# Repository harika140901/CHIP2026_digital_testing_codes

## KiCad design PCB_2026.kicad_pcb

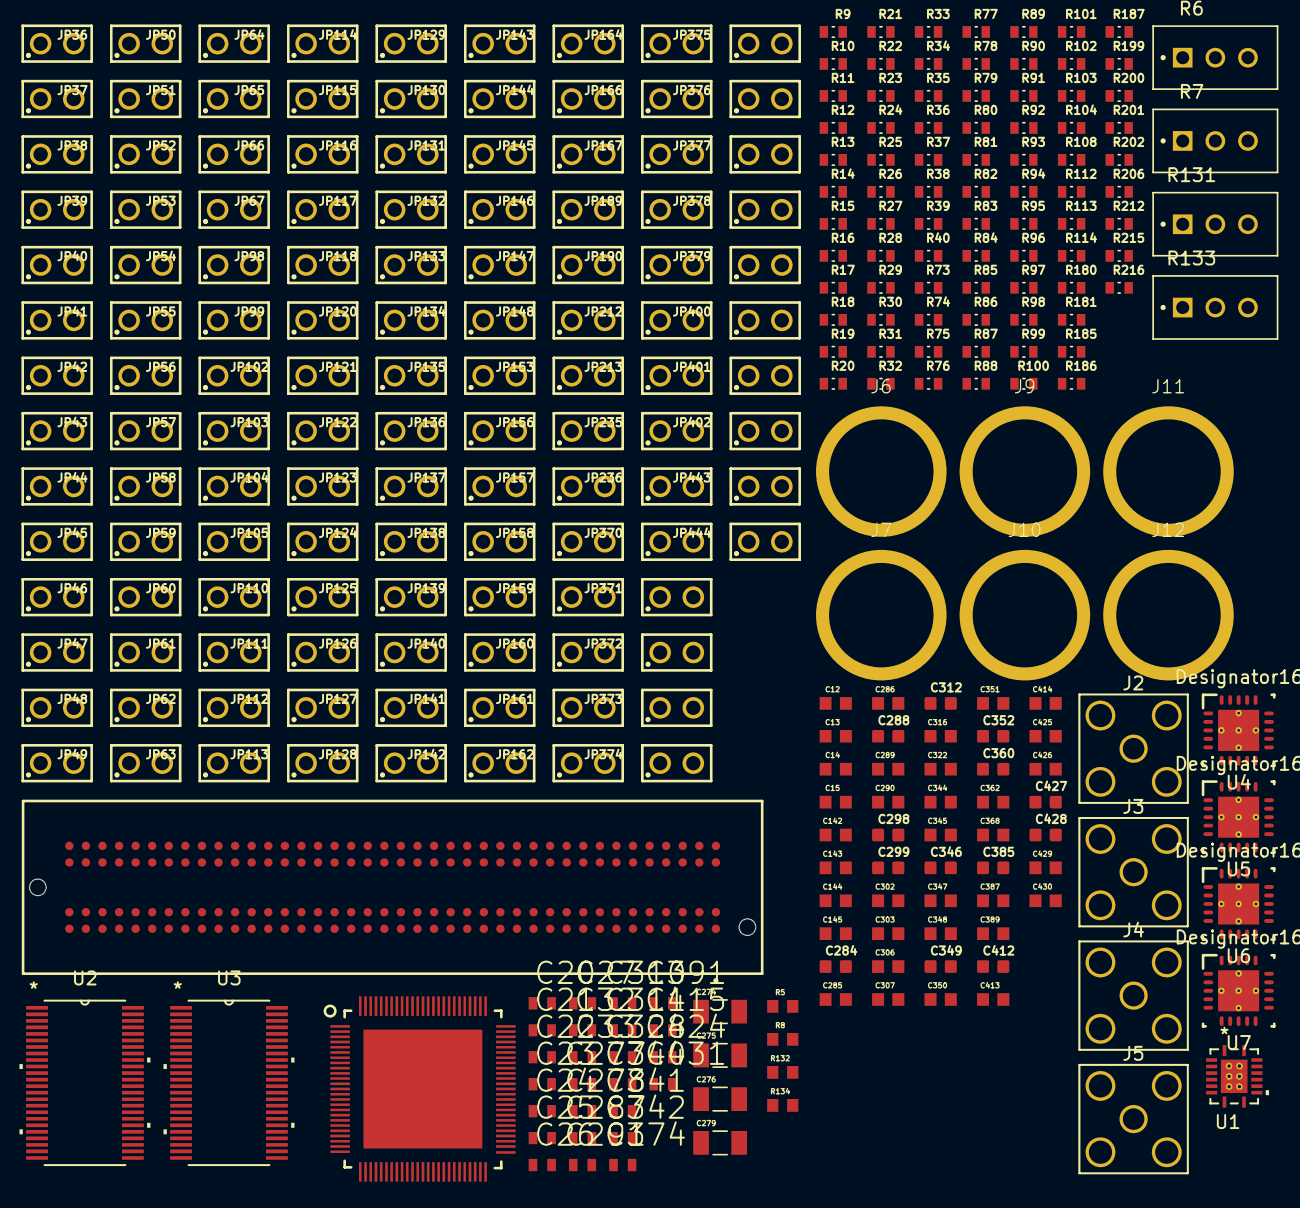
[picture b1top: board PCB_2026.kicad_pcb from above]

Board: 2 copper layers, 306 parts (0 on the bottom side), 260 nets, no tracks yet.

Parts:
C12, C14, C142, C144: 4.7u; CAPC1608X90N
C13, C15, C143, C145, C286, C290, C306, C307, C322, C345, C348, C351, C368, C389, C414, C425, C430: 1n; CAPC1608X90N
C20, C21, C22, C23, C24, C25, C26, C27, C32, C33: 1uF; CAPC1608X90N
C274, C275, C276, C279: C100u; CAPC3216X180N
C277, C278, C287, C291, C310, C311, C328, C340, C341, C342, C374, C391, C415, C424, C431: 1u; CAPC1608X90N
C284, C288, C298, C299, C312, C346, C349, C352, C360, C385, C412, C427, C428: 10n; CAPC1608X90N
C285, C289, C302, C303, C316, C344, C347, C350, C362, C387, C413, C426, C429: 100n; CAPC1608X90N
J1: ASP-134603-01; CONN160_4603-01_SAI
J2, J3, J4, J5: 142-0701-201; CONN_142-0701-201_CIN
J6, J7, J9, J10, J11, J12: BJACK
JP6, JP7, JP22, JP23, JP24, JP25, JP26, JP29, JP30, JP31, JP32, JP33, JP34, JP35, JP36, JP37, JP38, JP39, JP40, JP41, JP42, JP43, JP44, JP45, JP46, JP47, JP48, JP49, JP50, JP51, JP52, JP53, JP54, JP55, JP56, JP57, JP58, JP59, JP60, JP61, JP62, JP63, JP64, JP65, JP66, JP67, JP98, JP99, JP102, JP103, JP104, JP105, JP110, JP111, JP112, JP113, JP114, JP115, JP116, JP117, JP118, JP120, JP121, JP122, JP123, JP124, JP125, JP126, JP127, JP128, JP129, JP130, JP131, JP132, JP133, JP134, JP135, JP136, JP137, JP138, JP139, JP140, JP141, JP142, JP143, JP144, JP145, JP146, JP147, JP148, JP153, JP156, JP157, JP158, JP159, JP160, JP161, JP162, JP164, JP166, JP167, JP189, JP190, JP212, JP213, JP235, JP236, JP370, JP371, JP372, JP373, JP374, JP375, JP376, JP377, JP378, JP379, JP400, JP401, JP402, JP443, JP444: Jumper; 61300211121
R5, R8, R132, R134: 1kOhm; RESC1508X50N
R6: 2kOhms; TRIM_PV36W253C01B00
R7: 200 Ohms; TRIM_PV36W253C01B00
R9, R10, R11, R12, R13, R14, R15, R16, R17, R18, R19, R20, R21, R22, R23, R24, R25, R26, R27, R28, R29, R30, R31, R32, R33, R34, R35, R36, R37, R38, R39, R40, R73, R74, R75, R76, R77, R78, R79, R80, R81, R82, R83, R84, R85, R86, R87, R88, R89, R90, R91, R92, R93, R94, R95, R96, R97, R98, R99, R100, R101, R102, R103, R104, R108, R112, R113, R114: 10 ohm 1%; RES_ERJ3EKF10R0V
R131, R133: 5kOhms; TRIM_PV36W502C01B00
R180, R181, R185, R186, R187, R199, R200, R201, R202, R206, R212, R215, R216: 1 ohm 0603; RES_ERJ3EKF10R0V
U1: SN74AVC4T245RGYR; RGY16_2P55X2P05
U2, U3: SN74AVCH16T245GR; DGG48
U4, U5, U6, U7: TPS74401RGWT; RGW0020A
U43: QFN80

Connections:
/BL_PCHG: J1.102, JP116.1
/BL_PCHG_Q: JP140.2, U43.73 (BL_PCHG)
/CLKA: J1.107, JP117.1
/CLKB: J1.108, JP118.1
/CLK_NEG_Q: C278.2, U43.49 (CLK_NEG)
/CLK_OUT_PAD: J1.57, JP66.1
/CLK_OUT_PAD_Q: JP124.2, U43.41 (CLK_OUT_PAD)
/CLK_POS_Q: C277.2, U43.48 (CLK_POS)
/CLK_SA_B: J1.58, JP67.1
/CLK_SA_B_Q: JP125.2, U43.55 (CLK_SA_B)
/CLK_conn_+: C277.1, J2.1
/CLK_conn_-: C278.1, J3.1
/COMPUTE_EN: J1.10, JP34.1
/COMPUTE_EN_Q: JP50.2, U43.17 (COMPUTE_EN)
/CONTROL_EN: J1.27, JP43.1
/CONTROL_EN_Q: JP59.2, U43.34 (CONTROL_EN)
/CS_B<0>: J1.92, JP114.1
/CS_B<0>_Q: JP132.2, U43.69 (CS_B<0>)
/CS_B<1>: J1.90, JP113.1
/CS_B<1>_Q: JP131.2, U43.67 (CS_B<1>)
/DEBUG_SC_OUT<0>: J1.125, JP136.1
/DEBUG_SC_OUT<0>_Q: JP160.1, U43.28 (DEBUG_SC_OUT<0>)
/DEBUG_SC_OUT<1>: J1.124, JP144.1
/DEBUG_SC_OUT<1>_Q: JP162.1, U43.29 (DEBUG_SC_OUT<1>)
/EN_U4: JP26.1, U4.11 (EN)
/EN_U5: JP33.1, U5.11 (EN)
/EN_U41: JP374.1, U6.11 (EN)
/EN_U42: JP379.1, U7.11 (EN)
/FreqNegOut_Q: J5.1, U43.93 (FreqNegOut)
/FreqPosOut_Q: J4.1, U43.94 (FreqPosOut)
/MUX_OUT_PAD: J1.26, JP42.1
/MUX_OUT_PAD_Q: JP58.2, U43.33 (MUX_OUT_PAD)
/READ_EN: J1.61, JP103.1
/READ_EN_Q: JP127.2, U43.59 (READ_EN)
/SAMPLE_EDGE_TIME<0>: J1.51, JP46.1
/SAMPLE_EDGE_TIME<0>_Q: JP62.2, U43.37 (SAMPLE_EDGE_TIME<0>)
/SAMPLE_EDGE_TIME<1>: J1.52, JP47.1
/SAMPLE_EDGE_TIME<1>_Q: JP63.2, U43.38 (SAMPLE_EDGE_TIME<1>)
/SAMPLE_EDGE_TIME<2>: J1.54, JP48.1
/SAMPLE_EDGE_TIME<2>_Q: JP64.2, U43.39 (SAMPLE_EDGE_TIME<2>)
/SAMPLE_EDGE_TIME<3>: J1.55, JP49.1
/SAMPLE_EDGE_TIME<3>_Q: JP65.2, U43.40 (SAMPLE_EDGE_TIME<3>)
/SA_EN: J1.93, JP115.1
/SA_EN_Q: JP133.2, U43.71 (SA_EN)
/SCN_OUT: J1.127, JP137.1
/SCN_OUT_Q: JP161.1, U43.27 (SCN_OUT)
/SCN_SEL<0>: J1.86, JP110.1
/SCN_SEL<0>_Q: JP128.2, U43.65 (SCN_SEL<0>)
/SCN_SEL<1>: J1.87, JP111.1
/SCN_SEL<1>_Q: JP129.2, U43.63 (SCN_SEL<1>)
/SCN_SEL<2>: J1.89, JP112.1
/SCN_SEL<2>_Q: JP130.2, U43.61 (SCN_SEL<2>)
/VCCA_DIG_LS: JP104.1, JP105.1, JP147.1, JP148.1, JP158.1, JP159.1, JP164.1, JP372.2, JP373.2
/VCCB_DIG_LS: C22.1, C23.1, C24.1, C25.1, JP153.1, JP377.2, JP378.2, U2.7 (VCCB), U2.18 (VCCB), U3.7 (VCCB), U3.18 (VCCB)
/VDDA_0.9V: C288.1, C289.1, C290.1, C291.1, C298.1, C302.1, C306.1, C310.1, C340.1, C341.1, C342.1, C344.1, C345.1, C346.1, C347.1, C348.1, C349.1, C350.1, C351.1, C352.1, C424.1, C425.1, C426.1, C427.1, C428.1, C429.1, C430.1, C431.1, JP31.2, JP32.2, R181.1, R185.1, R200.1, R201.1, R202.1, R215.1, R216.2
/VDDA_chip: R181.2, R185.2, R200.2, R201.2, R202.2, R215.2, R216.1, U43.3 (vdda), U43.13 (vdda), U43.26 (vdda), U43.51 (vdda), U43.81 (vdda), U43.85 (vdda), U43.89 (vdda)
/VDDQ_1.8V: C284.1, C285.1, C286.1, C287.1, C299.1, C303.1, C307.1, C311.1, C312.1, C316.1, C322.1, C328.1, C360.1, C362.1, C368.1, C374.1, C385.1, C387.1, C389.1, C391.1, C412.1, C413.1, C414.1, C415.1, JP24.2, JP25.2, R180.1, R186.1, R187.1, R199.2, R206.2, R212.1
/VDD_5V: C275.1, JP7.2, JP401.2, JP443.1, JP444.1
/VDD_5VD: C276.1, JP143.2, JP370.2, JP371.2, JP374.2, JP375.2, JP376.2, JP379.2, JP402.2, JP443.2, JP444.2
/VDD_5VD_JACK: J7.1 (1_1), JP143.1, JP402.1
/VDD_5V_JACK: J11.1 (1_1), JP7.1, JP401.1
/VDD_5V_U4: C12.1, JP22.1, JP23.1, U4.5 (IN), U4.6 (IN), U4.7 (IN), U4.8 (IN), U4.10 (BIAS)
/VDD_5V_U5: C14.1, JP29.1, JP30.1, U5.5 (IN), U5.6 (IN), U5.7 (IN), U5.8 (IN), U5.10 (BIAS)
/VDD_5V_U41: C142.1, JP370.1, JP371.1, U6.5 (IN), U6.6 (IN), U6.7 (IN), U6.8 (IN), U6.10 (BIAS)
/VDD_5V_U42: C144.1, JP375.1, JP376.1, U7.5 (IN), U7.6 (IN), U7.7 (IN), U7.8 (IN), U7.10 (BIAS)
/VDD_5V_a: C274.1, JP6.2, JP22.2, JP23.2, JP26.2, JP29.2, JP30.2, JP33.2, JP400.2
/VDD_5V_a_JACK: J6.1 (1_1), JP6.1, JP400.1
/VDD_N5V: C279.1, JP235.2, JP236.2
/VDD_N5V_JACK: J12.1 (1_1), JP235.1, JP236.1
/VFB_U4: R5.2, R6.2, R6.3, U4.16 (FB)
/VFB_U5: R7.2, R7.3, R8.2, U5.16 (FB)
/VFB_U41: R131.2, R131.3, R132.2, U6.16 (FB)
/VFB_U42: R133.2, R133.3, R134.2, U7.16 (FB)
/VOUT_U4: JP24.1, JP25.1, R6.1, U4.1 (OUT), U4.18 (OUT), U4.19 (OUT), U4.20 (OUT)
/VOUT_U5: JP31.1, JP32.1, R7.1, U5.1 (OUT), U5.18 (OUT), U5.19 (OUT), U5.20 (OUT)
/VOUT_U41: JP372.1, JP373.1, R131.1, U6.1 (OUT), U6.18 (OUT), U6.19 (OUT), U6.20 (OUT)
/VOUT_U42: JP377.1, JP378.1, R133.1, U7.1 (OUT), U7.18 (OUT), U7.19 (OUT), U7.20 (OUT)
/WEN: J1.60, JP102.1
/WEN_Q: JP126.2, U43.57 (WEN)
/WL_EN: J1.113, JP121.1
/WL_EN_Q: JP146.2, U43.99 (WL_EN)
/capturestart<0>_Q: JP51.2, U43.19 (capturestart<0>_)
/capturestart<1>_Q: JP52.2, U43.21 (capturestart<1>_)
/capturestart<2>_Q: JP53.2, U43.23 (capturestart<2>_)
/capturestart<3>_Q: JP54.2, U43.25 (capturestart<3>_)
/div_ratio<0>: J1.19, JP39.1
/div_ratio<0>_Q: JP55.2, U43.30 (div_ratio<0>)
/div_ratio<1>: J1.22, JP40.1
/div_ratio<1>_Q: JP56.2, U43.31 (div_ratio<1>)
/div_ratio<2>: J1.48, JP44.1
/div_ratio<2>_Q: JP60.2, U43.35 (div_ratio<2>)
/div_ratio<3>: J1.49, JP45.1
/div_ratio<3>_Q: JP61.2, U43.36 (div_ratio<3>)
/osc_EN: J1.111, JP120.1
/osc_EN_Q: JP145.2, U43.95 (osc_EN)
GND: C12.2, C13.2, C14.2, C15.2, C20.2, C21.2, C22.2, C23.2, C24.2, C25.2, C26.2, C27.2, C32.2, C33.2, C142.2, C143.2, C144.2, C145.2, C274.2, C275.2, C276.2, C279.2, C284.2, C285.2, C286.2, C287.2, C288.2, C289.2, C290.2, C291.2, C298.2, C299.2, C302.2, C303.2, C306.2, C307.2, C310.2, C311.2, C312.2, C316.2, C322.2, C328.2, C340.2, C341.2, C342.2, C344.2, C345.2, C346.2, C347.2, C348.2, C349.2, C350.2, C351.2, C352.2, C360.2, C362.2, C368.2, C374.2, C385.2, C387.2, C389.2, C391.2, C412.2, C413.2, C414.2, C415.2, C424.2, C425.2, C426.2, C427.2, C428.2, C429.2, C430.2, C431.2, J1.1, J1.4, J1.5, J1.8, J1.9, J1.12, J1.13, J1.16, J1.17, J1.20, J1.21, J1.24, J1.25, J1.28, J1.29, J1.32, J1.33, J1.36, J1.38, J1.40, J1.42, J1.43, J1.46, J1.47, J1.50, J1.53, J1.56, J1.59, J1.62, J1.65, J1.68, J1.75, J1.77, J1.79, J1.81, J1.84, J1.85, J1.88, J1.91, J1.94, J1.97, J1.100, J1.103, J1.106, J1.109, J1.112, J1.115, J1.118, J1.120, J1.123, J1.126, J1.129, J1.132, J1.135, J1.138, J1.141, J1.144, J1.147, J1.150, J1.153, J1.156, J1.159, J2.2, J2.3, J2.4, J2.5, J3.2, J3.3, J3.4, J3.5, J4.2, J4.3, J4.4, J4.5, J5.2, J5.3, J5.4, J5.5, J9.1 (1_1), J10.1 (1_1), JP98.2, JP99.2, JP122.2, JP123.2, JP134.1, JP135.1, JP138.1, JP139.1, JP156.1, JP157.1, JP166.1, JP166.2, JP167.1, JP167.2, JP189.1, JP189.2, JP190.1, JP190.2, JP212.1, JP212.2, JP213.1, JP213.2, R5.1, R8.1, R132.1, R134.1, U1.8 (GND), U1.9 (GND), U1.17 (EPAD), U2.4 (GND), U2.10 (GND), U2.15 (GND), U2.21 (GND), U2.28 (GND), U2.34 (GND), U2.39 (GND), U2.45 (GND), U3.4 (GND), U3.10 (GND), U3.15 (GND), U3.21 (GND), U3.28 (GND), U3.34 (GND), U3.39 (GND), U3.45 (GND), U4.2 (NC), U4.3 (NC), U4.4 (NC), U4.12 (GND), U4.13 (NC), U4.14 (NC), U4.17 (NC), U4.21 (PAD), U5.2 (NC), U5.3 (NC), U5.4 (NC), U5.12 (GND), U5.13 (NC), U5.14 (NC), U5.17 (NC), U5.21 (PAD), U6.2 (NC), U6.3 (NC), U6.4 (NC), U6.12 (GND), U6.13 (NC), U6.14 (NC), U6.17 (NC), U6.21 (PAD), U7.2 (NC), U7.3 (NC), U7.4 (NC), U7.12 (GND), U7.13 (NC), U7.14 (NC), U7.17 (NC), U7.21 (PAD), U43.1 (gnda), U43.2 (NC), U43.4 (NC), U43.6 (NC), U43.7 (gnda), U43.8 (NC), U43.10 (NC), U43.11 (gnda), U43.12 (NC), U43.14 (NC), U43.15 (gnda), U43.16 (NC), U43.18 (NC), U43.20 (NC), U43.22 (NC), U43.24 (NC), U43.42 (gnda), U43.43 (gnda), U43.44 (gnda), U43.45 (gnda), U43.46 (gnda), U43.47 (gnda), U43.52 (NC), U43.54 (NC), U43.56 (NC), U43.58 (NC), U43.60 (NC), U43.62 (NC), U43.64 (NC), U43.66 (NC), U43.68 (NC), U43.70 (NC), U43.72 (NC), U43.74 (Nc), U43.75 (gnda), U43.82 (gnda), U43.83 (gnda), U43.84 (gnda), U43.86 (gnda), U43.87 (gnda), U43.88 (gnda), U43.90 (gnda), U43.91 (gnda), U43.92 (gnda), U43.96 (gnda), U43.97 (gnda), U43.98 (gnda), U43.101 (THERM)
unnamed: C20.1, JP105.2, U2.31 (VCCA)
unnamed: C21.1, JP104.2, U2.42 (VCCA)
unnamed: C26.1, JP147.2, U3.42 (VCCA)
unnamed: C27.1, JP148.2, U3.31 (VCCA)
unnamed: JP34.2, R9.1
unnamed: JP35.2, R10.1
unnamed: JP36.2, R11.1
unnamed: JP37.2, R12.1
unnamed: JP38.2, R13.1
unnamed: JP39.2, R14.1
unnamed: JP40.2, R15.1
unnamed: JP41.2, R16.1
unnamed: JP42.2, R17.1
unnamed: JP43.2, R18.1
unnamed: JP44.2, R19.1
unnamed: JP45.2, R20.1
unnamed: JP46.2, R21.1
unnamed: JP47.2, R22.1
unnamed: JP48.2, R23.1
unnamed: JP49.2, R24.1
unnamed: JP50.1, R25.2
unnamed: JP51.1, R26.2
unnamed: JP52.1, R27.1
unnamed: JP53.1, R28.2
unnamed: JP54.1, R29.2
unnamed: JP55.1, R30.2
unnamed: JP56.1, R31.2
unnamed: JP57.1, R32.2
unnamed: JP58.1, R33.2
unnamed: JP59.1, R34.2
unnamed: JP60.1, R35.2
unnamed: JP61.1, R36.2
unnamed: JP62.1, R37.2
unnamed: JP63.1, R38.2
unnamed: JP64.1, R39.2
unnamed: JP65.1, R40.2
unnamed: JP66.2, R73.1
unnamed: JP67.2, R74.1
unnamed: JP102.2, R75.1
unnamed: JP103.2, R76.1
unnamed: JP110.2, R77.1
unnamed: JP111.2, R78.1
unnamed: JP112.2, R79.1
unnamed: JP113.2, R80.1
unnamed: JP114.2, R81.1
unnamed: JP115.2, R82.1
unnamed: JP116.2, R83.1
unnamed: JP117.2, R84.1
unnamed: JP118.2, R85.1
unnamed: JP120.2, R87.1
unnamed: JP121.2, R88.1
unnamed: JP124.1, R89.2
unnamed: JP125.1, R90.2
unnamed: JP126.1, R91.1
unnamed: JP127.1, R92.2
unnamed: JP128.1, R93.2
unnamed: JP129.1, R94.2
unnamed: JP130.1, R95.2
unnamed: JP131.1, R96.2
unnamed: JP132.1, R97.2
unnamed: JP133.1, R98.2
unnamed: JP136.2, R86.1
unnamed: JP137.2, R102.1
unnamed: JP140.1, R99.2
unnamed: JP141.1, R100.2
unnamed: JP142.1, R101.2
unnamed: JP144.2, R108.1
unnamed: JP145.1, R103.2
unnamed: JP146.1, R104.2
unnamed: JP160.2, R112.1
unnamed: JP161.2, R113.1
unnamed: JP162.2, R114.1
unnamed: R180.2, U43.9 (vddq)
unnamed: R186.2, U43.5 (vddq)
unnamed: R187.2, U43.100 (vddq)
unnamed: R199.1, U43.76 (vddq)
unnamed: R206.1, U43.53 (vddq)
unnamed: R212.2, U43.50 (vddq)
unnamed: R114.2, U1.5 (1A2)
unnamed: R108.2, U1.12 (1B2)
unnamed: JP159.2, U1.2 (1DIR)
unnamed: R113.2, U1.6 (2A1)
unnamed: R112.2, U1.7 (2A2)
unnamed: R102.2, U1.11 (2B1)
unnamed: R86.2, U1.10 (2B2)
unnamed: JP158.2, U1.3 (2DIR)
unnamed: C33.1, JP164.2, U1.1 (VCCA)
unnamed: C32.1, JP153.2, U1.16 (VCCB)
unnamed: JP157.2, U1.15 (~1OE)
unnamed: JP156.2, U1.14 (~2OE)
unnamed: R25.1, U2.47 (1A1)
unnamed: R26.1, U2.46 (1A2)
unnamed: R27.2, U2.44 (1A3)
unnamed: R28.1, U2.43 (1A4)
unnamed: R29.1, U2.41 (1A5)
unnamed: R30.1, U2.40 (1A6)
unnamed: R31.1, U2.38 (1A7)
unnamed: R32.1, U2.37 (1A8)
unnamed: R9.2, U2.2 (1B1)
unnamed: R10.2, U2.3 (1B2)
unnamed: R11.2, U2.5 (1B3)
unnamed: R12.2, U2.6 (1B4)
unnamed: R13.2, U2.8 (1B5)
unnamed: R14.2, U2.9 (1B6)
unnamed: R15.2, U2.11 (1B7)
unnamed: R16.2, U2.12 (1B8)
unnamed: JP134.2, U2.1 (1DIR)
unnamed: R33.1, U2.36 (2A1)
unnamed: R34.1, U2.35 (2A2)
unnamed: R35.1, U2.33 (2A3)
unnamed: R36.1, U2.32 (2A4)
unnamed: R37.1, U2.30 (2A5)
unnamed: R38.1, U2.29 (2A6)
unnamed: R39.1, U2.27 (2A7)
unnamed: R40.1, U2.26 (2A8)
unnamed: R17.2, U2.13 (2B1)
unnamed: R18.2, U2.14 (2B2)
unnamed: R19.2, U2.16 (2B3)
unnamed: R20.2, U2.17 (2B4)
unnamed: R21.2, U2.19 (2B5)
unnamed: R22.2, U2.20 (2B6)
unnamed: R23.2, U2.22 (2B7)
unnamed: R24.2, U2.23 (2B8)
unnamed: JP135.2, U2.24 (2DIR)
unnamed: JP98.1, U2.48 (~1OE)
unnamed: JP99.1, U2.25 (~2OE)
unnamed: R89.1, U3.47 (1A1)
unnamed: R90.1, U3.46 (1A2)
unnamed: R91.2, U3.44 (1A3)
unnamed: R92.1, U3.43 (1A4)
unnamed: R93.1, U3.41 (1A5)
unnamed: R94.1, U3.40 (1A6)
unnamed: R95.1, U3.38 (1A7)
unnamed: R96.1, U3.37 (1A8)
unnamed: R73.2, U3.2 (1B1)
unnamed: R74.2, U3.3 (1B2)
unnamed: R75.2, U3.5 (1B3)
unnamed: R76.2, U3.6 (1B4)
unnamed: R77.2, U3.8 (1B5)
unnamed: R78.2, U3.9 (1B6)
unnamed: R79.2, U3.11 (1B7)
unnamed: R80.2, U3.12 (1B8)
unnamed: JP138.2, U3.1 (1DIR)
unnamed: R97.1, U3.36 (2A1)
unnamed: R98.1, U3.35 (2A2)
unnamed: R99.1, U3.33 (2A3)
unnamed: R100.1, U3.32 (2A4)
unnamed: R101.1, U3.30 (2A5)
unnamed: R103.1, U3.27 (2A7)
unnamed: R104.1, U3.26 (2A8)
unnamed: R81.2, U3.13 (2B1)
unnamed: R82.2, U3.14 (2B2)
unnamed: R83.2, U3.16 (2B3)
unnamed: R84.2, U3.17 (2B4)
unnamed: R85.2, U3.19 (2B5)
unnamed: R87.2, U3.22 (2B7)
unnamed: R88.2, U3.23 (2B8)
unnamed: JP139.2, U3.24 (2DIR)
unnamed: JP122.1, U3.48 (~1OE)
unnamed: JP123.1, U3.25 (~2OE)
unnamed: C13.1, U4.15 (SS)
unnamed: C15.1, U5.15 (SS)
unnamed: C143.1, U6.15 (SS)
unnamed: C145.1, U7.15 (SS)

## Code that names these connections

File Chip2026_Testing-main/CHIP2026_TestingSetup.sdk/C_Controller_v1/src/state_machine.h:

#ifndef SRC_STATE_MACHINE_H_
#define SRC_STATE_MACHINE_H_

// custom header files
#include "utils.h"
#include "echo.h"

#include "xgpio.h"
#include "xaxidma.h"
#include "xparameters.h"

/********** Signal Index for Dig AXI IN Bus 0 **********/
#define BANK_EN_0  	0
#define BANK_EN_1  	1
#define BANK_EN_2  	2
#define BANK_EN_3  	3
#define WL_EN		4
#define SA_EN		5
#define BL_PCHG		6
#define CLK_SA		7
#define WRITE_EN	8
#define CS_0		9
#define CS_1		10
#define SCN_SEL_0	11
#define SCN_SEL_1	12
#define SCN_SEL_2	13
#define SCN_SEL_3	14
#define InputEN_DAC 15
#define CALIB_EN	16
#define BANK_SEL	17
#define CHG_EN		18
#define RST_CAP		19
#define VDAC_CTRL	20
#define VTC_EN		21
#define TDC_EN		22
#define TDC_RST		23
#define TDC_COMPUTE 24
#define DFF_RST		25
#define CTRL_EN		26
#define CLK_A		27
#define CLK_B		28
#define IN_EN		29
#define SCN_IN		30
#define CTRL_VB		31

/********** Signal Index for Dig AXI IN Bus 1 **********/
#define CTRL_VBP	32
#define CTRL_VBN	33

/********** Signal Index for Output AXI Bus **********/
#define SCN_OUT 0
#define IMC_DONE 1

// Define Scan Chains
#define TDC_OUT_SC_LM       0
#define TDC_OUT_SC_RM       1
#define CL_EN_SC_LM         2
#define CL_EN_SC_RM         3
#define WL_SC               4
#define SA_OUT_SC           5
#define WRITE_DATA_SC       6
#define CONTROL_LOGIC_SC    7
#define XIN_SC_QUADV        8
#define XIN_SC_UNITV        9

#define MAX_SCAN_LEN 1164
#define NUM_WL 1164

// Scan chain validation + DMA length helpers
static inline int is_valid_scan_id(u8 scan_id) {
    return (scan_id <= XIN_SC_UNITV);
}

static inline u16 get_scan_len_for_id(u8 scan_id) {
    if (!is_valid_scan_id(scan_id)) {
        return 0;
    }
    // this is valid for the controller-side default table
    // if you later want a different table, set this here
    return 1152;
}

static inline u32 scan_dma_len_bytes(u16 scan_len) {
    return (((u32)scan_len + 31u) / 32u) * 4u;
}

//Define signal index for MODE_SETIING_AXI
#define VERILOG_C_SCAN 	0
#define SCAN_SEL_0_V 	1
#define SCAN_SEL_1_V 	2
#define SCAN_SEL_2_V 	3
#define SCAN_SEL_3_V 	4
#define SCAN_IN_RECV_V 	5
#define SCAN_IN_SEND_V 	6
#define SCAN_IN_EN_V 	7
#define SCAN_OUT_EN_V 	8
#define Test_DMA_V 		9
#define NCLK_0_V 		10
#define NCLK_1_V 		11
#define NCLK_2_V 		12
#define NCLK_3_V 		13
#define NCLK_4_V 		14
#define NCLK_5_V 		15
#define NCLK_6_V 		16
#define NCLK_7_V 		17
#define TOPS_EN_V 		18
#define TOPS_STOP_V 	19
#define WRITE_SRAM_EN_V 20
#define FAST_IMC_EN_V 	21
#define SEND_IMC_DATA_V 22
#define IMC_Mode 		23
#define Ext_IMC_EN		24
#define stepIMC_EN		25
#define SCAN_LEN_V_0	26
#define SCAN_LEN_V_1	27
#define SCAN_LEN_V_2	28
#define SCAN_LEN_V_3	29
#define SCAN_LEN_V_4	30
#define SCAN_LEN_V_5	31

//Create a structure to store the state machine data.
struct SM_DATA{
    u8 signal_values[DIG_IN_SIG_LEN];
    u8 default_signal_values[DIG_IN_SIG_LEN];

    u8 mode_signal_values[32];
    u8 mode_default_signal_values[32];

    u8 dma_scanout_buffer[148] __attribute__((aligned(32)));
    u8 dma_scan_in_buffer[148] __attribute__((aligned(32)));
    u8 dma_imcout_buffer[452] __attribute__((aligned(32)));

    int imc_out_mac[360];
    u8 sram_read_buffer [36*1164];
    u8 sram_write_buffer[36*1152];
    u16 calib_wl[12];
    u16 scan_len[10];

    XGpio AXI_INPUT_BUS_0;
    XGpio AXI_INPUT_BUS_1;
    XGpio AXI_OUTPUT_BUS;
    XGpio AXI_DEBUG_OUTPUT_BUS_0;
    XGpio AXI_DEBUG_OUTPUT_BUS_1;
    XGpio AXI_SCAN_MODE_SETTINGS_BUS;
    XAxiDma AxiDma;

    float Correction_Data[2][4][90];
};

extern struct SM_DATA GLOBAL_SM_DATA;

err_t process_fn();
#endif /* SRC_STATE_MACHINE_H_ */
